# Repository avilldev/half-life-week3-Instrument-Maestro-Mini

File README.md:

# Maestro Mini

The Maestro Mini is a device that can give you all the notes in an octave and can also play a tune! It is useful to use in tuning and ear training.

## Components

* **Microcontroller:** Seeed Studio XIAO ESP32-C3
* **I/O Expander:** MCP23017
* **Audio Output:** PAM8302 Audio Amplifier
* **Display:** 0.96" OLED
* **Inputs:** 10x Cherry MX Mechanical Switches
* **Passive Components:**
* 2x 4.7kΩ resistors (I2C pull-ups)
* 1x 1kΩ resistor and 1x 100nF ceramic capacitor (audio smoothing filter)
* **Base:** Custom PCB

## Gallery

## BOM

| Item                          | Qty | Supplier | Cost/item | Total Cost | link                                                                                                                                                     |
| ----------------------------- | --- | -------- | --------- | ---------- | -------------------------------------------------------------------------------------------------------------------------------------------------------- |
| 100nF Capacitor               | 1   | Alibaba  | $0.58     | $0.58      | https://www.alibaba.com/product-detail/AI-KSEN-Ceramic-Capacitor-104-0_1601772197711.html?spm=a2756.trade-carp.valid-supplier.2.5681319248yVoc           |
| 4.7k Ohms Resistor            | 2   | Alibaba  | $0.26     | $0.52      | https://www.alibaba.com/product-detail/1W-Metal-Film-Resistor-0-47_1601524142362.html?spm=a2756.trade-carp.valid-supplier.2.56813192Smr3bg               |
| 1k Ohms Resistor              | 1   | Owned    | $0.00     | $0.00      |                                                                                                                                                          |
| MX Cherry Mechanical Keyboard | 10  | Alibaba  | $0.15     | $1.50      | https://www.alibaba.com/product-detail/MX-Cherry-Mechanical-Keyboard-with-Black_1601730062197.html?spm=a2756.trade-carp.valid-supplier.2.56813192Smr3bg  |
| 0.96 Inch OLED                | 1   | Alibaba  | $1.15     | $1.15      | https://www.alibaba.com/product-detail/0-96-Inch-OLED-Module-White_1601198774090.html?spm=a2756.trade-carp.valid-supplier.2.56813192Smr3bg               |
| PAM8302 Amplifier             | 1   | Alibaba  | $0.38     | $0.38      | https://www.alibaba.com/product-detail/PAM8302-ICs-Module-2-5W-Mono_1601517012954.html?spm=a2756.trade-carp.valid-supplier.2.56813192Smr3bg              |
| Seeed Studio XIAO ESP32-C3    | 1   | Alibaba  | $5.84     | $5.84      | https://www.alibaba.com/product-detail/Seeed-Studio-XIAO-ESP32C6-ESP32S3-ESP32S3_1601286855889.html?spm=a2756.trade-carp.valid-supplier.2.56813192Smr3bg |
| PCB Board                     | 1   | JLCPCB   | $9.60     | $9.60      | https://jlcpcb.com/                                                                                                                                      |
| MCP23017 DIP-28               | 1   | Alibaba  | $1.06     | $1.06      | https://www.alibaba.com/product-detail/DIP-28-MCP23017-16-Bit-I_1601965185059.html?spm=a2756.trade-carp.valid-supplier.2.568131927N48zy                  |
| **Parts subtotal**            | —   | —        | —         | **$20.63** | —                                                                                                                                                        |
| **Tax & shipping**            | —   | —        | —         | **$24.13** | —                                                                                                                                                        |
| **Total**                     | —   | —        | —         | **$44.76** | —                                                                                                                                                        |

Out of tier 2, $65 funding.

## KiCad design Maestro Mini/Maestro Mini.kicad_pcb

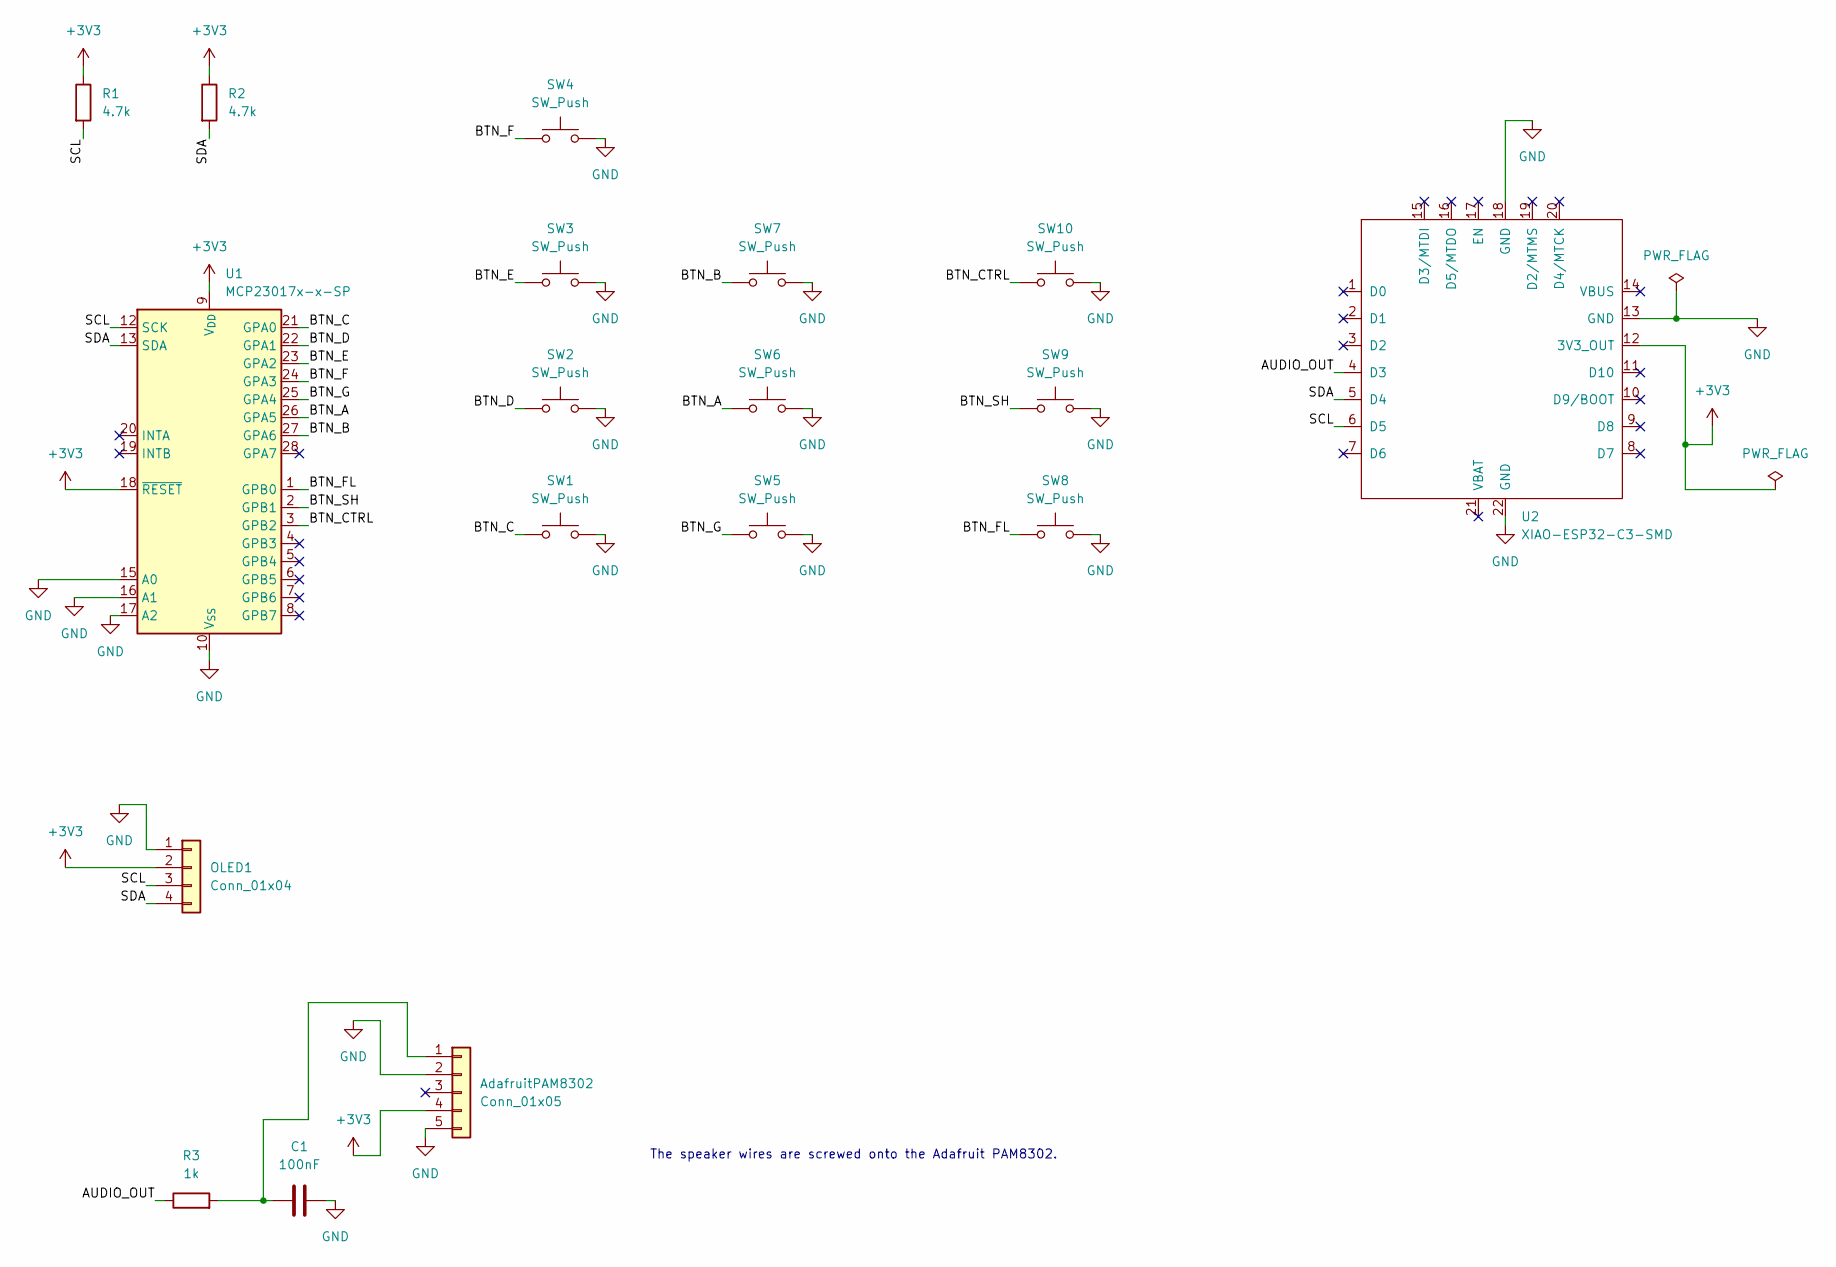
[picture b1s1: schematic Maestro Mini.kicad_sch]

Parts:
AdafruitPAM8302: Conn_01x05; PinHeader_1x05_P2.54mm_Vertical
C1: 100nF; C_Disc_D5.0mm_W2.5mm_P5.00mm
OLED1: Conn_01x04; Display_128x64_096_I2C
R1, R2: 4.7k; R_Axial_DIN0204_L3.6mm_D1.6mm_P7.62mm_Horizontal
R3: 1k; R_Axial_DIN0204_L3.6mm_D1.6mm_P7.62mm_Horizontal
SW1, SW2, SW3, SW4, SW5, SW6, SW7, SW8, SW9, SW10: SW_Push; SW_Cherry_MX_1.00u_PCB
U1: MCP23017x-x-SP; DIP-28_W7.62mm
U2: XIAO-ESP32-C3-SMD

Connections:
+3V3: AdafruitPAM8302.4, OLED1.2, R1.1, R2.1, U1.9 (V_{DD}), U1.18 (~RESET), U2.12 (3V3_OUT)
/AUDIO_OUT: R3.1, U2.4 (D3)
/BTN_A: SW6.1, U1.26 (GPA5)
/BTN_B: SW7.1, U1.27 (GPA6)
/BTN_C: SW1.1, U1.21 (GPA0)
/BTN_CTRL: SW10.1, U1.3 (GPB2)
/BTN_D: SW2.1, U1.22 (GPA1)
/BTN_E: SW3.1, U1.23 (GPA2)
/BTN_F: SW4.1, U1.24 (GPA3)
/BTN_FL: SW8.1, U1.1 (GPB0)
/BTN_G: SW5.1, U1.25 (GPA4)
/BTN_SH: SW9.1, U1.2 (GPB1)
/SCL: OLED1.3, R1.2, U1.12 (SCK), U2.6 (D5)
/SDA: OLED1.4, R2.2, U1.13 (SDA), U2.5 (D4)
GND: AdafruitPAM8302.2, AdafruitPAM8302.5, C1.2, OLED1.1, SW1.2, SW2.2, SW3.2, SW4.2, SW5.2, SW6.2, SW7.2, SW8.2, SW9.2, SW10.2, U1.10 (V_{SS}), U1.15 (A0), U1.16 (A1), U1.17 (A2), U2.13 (GND), U2.18 (GND), U2.22 (GND)
unnamed: AdafruitPAM8302.1, C1.1, R3.2

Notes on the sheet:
The speaker wires are screwed onto the Adafruit PAM8302.

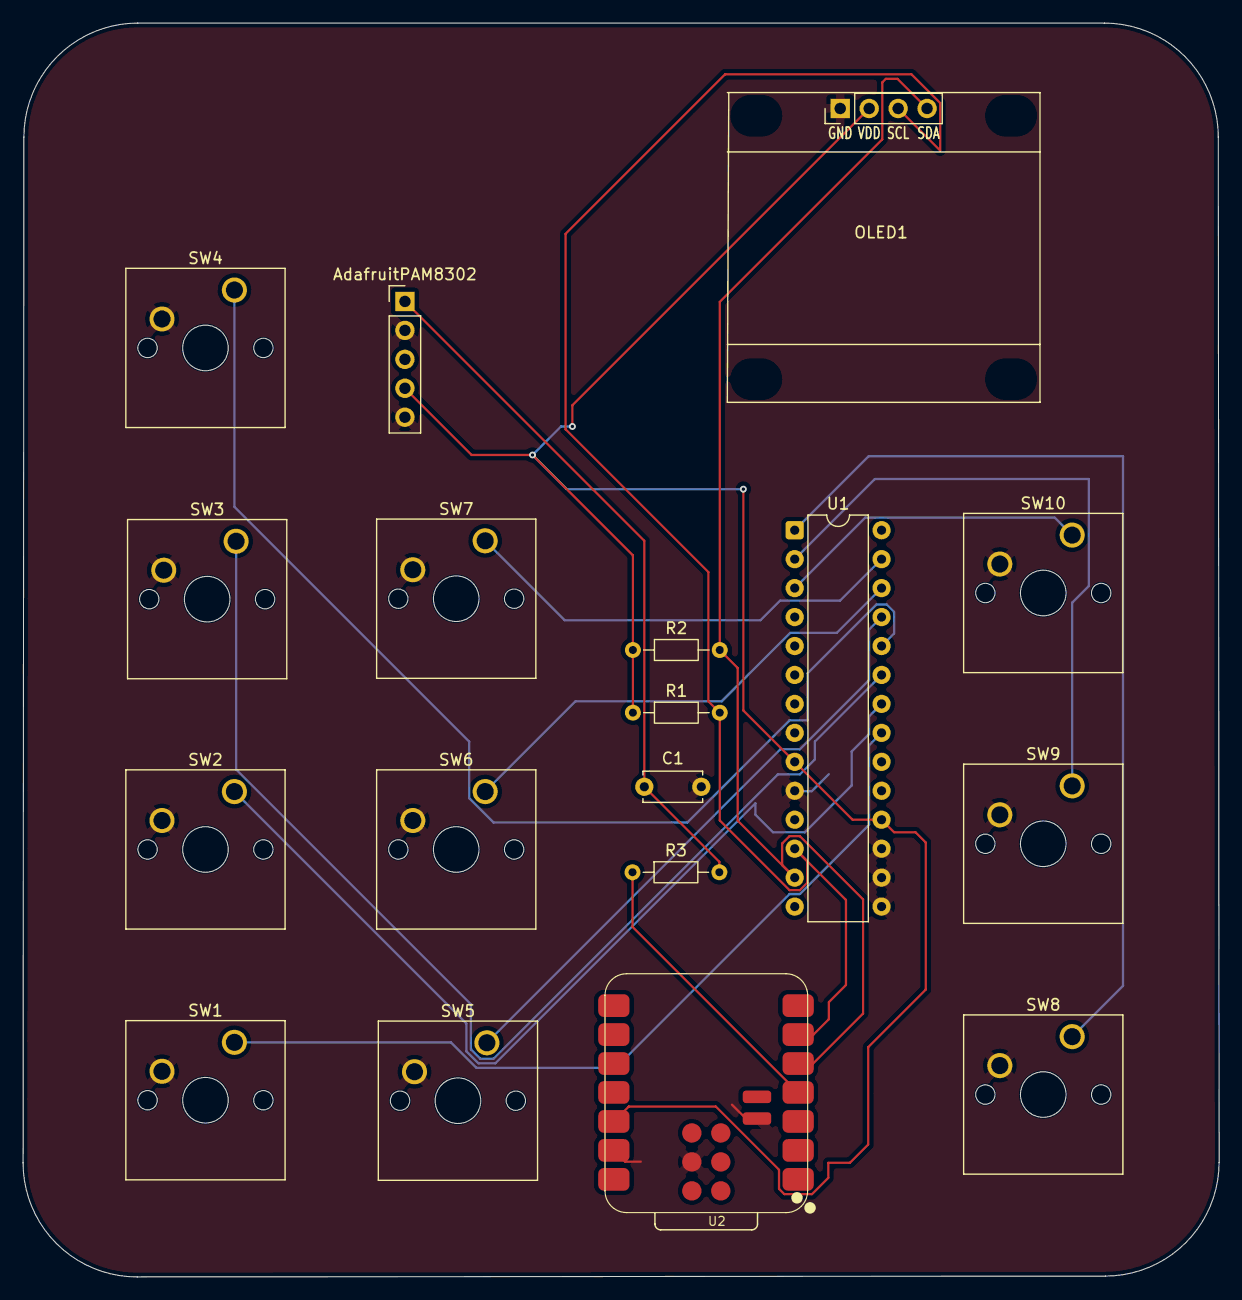
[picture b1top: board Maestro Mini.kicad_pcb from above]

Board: 2 copper layers, 104.9 x 110.0 mm, 18 parts (0 on the bottom side), 16 nets.
